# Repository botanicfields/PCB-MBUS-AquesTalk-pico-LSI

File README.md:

# PCB-MBUS-AquesTalk-pico-LSI
# M5Stack用 AquesTalk pico LSIモジュール基板
M-BUS Module of AquesTalk pico LSI for M5Stack

# 1. 概要
　市販の音声合成専用LSI「AquesTalk pico LSI」（別売）をM-BUSモジュールとしてM5Stackに取り付けるための半完成基板です。  
　AquesTalk pico LSIの詳細は、データシートを参照ください。  
[Data Sheet: 音声合成 LSI 「AquesTalk pico LSI」ATP3011](https://www.a-quest.com/archive/manual/atp3011_datasheet.pdf)  
[Data Sheet: 音声合成 LSI 「AquesTalk pico LSI」ATP3012](https://www.a-quest.com/archive/manual/atp3012_datasheet.pdf)

### 基板V04の変更点
　2022年10月末から基板V04を提供しています。詳細は、スピーカーの接続の項を参照ください。

- ハンダジャンパJP8, JP9を追加しました。
- ランドJ5を追加しました。

### 委託販売
（スイッチサイエンス扱い）[M5Stack用 AquesTalk pico LSI モジュール基板](https://www.switch-science.com/collections/marketplace/products/7624)

### 動作例
（YouTube）["AquesTalk pico LSI" speaks date and time](https://youtu.be/DpDmjqU7RUM)  
（YouTube）[M-Bus Module of AquesTalk pico LSI drives the built-in speaker of M5Stack](https://youtu.be/npRQEOJegkY)  
（YouTube）[M-Bus Module of AquesTalk pico LSI for M5Stack](https://youtu.be/YfKwWRxrInM)  
（YouTube）[M-Bus Module of AquesTalk pico LSI for M5Stack on Core2](https://youtu.be/zXvg78xzJ5E)

### 組み立て例
　組み立てにはハンダ付けが必要です。

左側: ATP3011を搭載、音声アナログ信号をGPIO35に入力するためJP5をショート  
右側: ATP3012を搭載、音声アナログ信号をGPIO35に入力するためJP6をショート  
   
写真右: M5Stack 取り付け例、J4に外部スピーカを接続  

## 1.1 特徴
- AquesTalk pico LSI（28ピンDIPタイプ）1個を搭載できます。
- ATP3011, ATP3012の両方に対応しています。
- パワーアンプ（LM4871）を内蔵し、スピーカーを直接駆動できます。
- AquestTalk pico LSIを3.3Vで動作させ、M-BUSに直結できます。
- プロトモジュールのモールド（別売）を流用し、M5Stackに取り付けできます。
- スピーカー以外のケーブル接続が不要です。
- DIP スイッチで動作モード・通信モードを設定できます。
- インタフェースをI2C, UART, SPIから選べます。
- AquesTalk pico LSIの音声出力をM-BUSから取り込めます。
- M5StackのリセットでAquesTalk pico LSIをリセットします。
- スタンドアロンモードのためのランドがあります。

DIP: Dual In-line Package  
I2C: Inte-Integrated Circuit  
UART: Universal Asynchronous Receiver Transmitter  
SPI: Serial Peripheral Interface

## 1.2 商品内容
- M-BUS モジュール基板（半完成品）1枚  
- スピーカーケーブル 1組（2ピンPH相当コネクタ付き、20cm片端ストリップ済）  
（秋月電子通商扱い）[コネクタ付コード２Ｐ（Ａ）（赤白）DG01032-0045-01(C5679)](https://akizukidenshi.com/catalog/g/gC-05679/)
- 説明書 1部

※ AquesTalk pico LSIは付属しません。  
※ プロトモジュールのモールドは付属しません。  
※ スピーカーは付属しません。

### 商品写真
写真左: 内容物(基板V4)、写真右: 基板V4裏面  

## 1.3 別途必要なもの
- AquesTalk pico LSI（秋月電子通商扱い）  
[音声合成ＬＳＩ　ＡＴＰ３０１１Ｆ１－ＰＵ（ゆっくりな女性の音声）
ATP3011F1-PU](https://akizukidenshi.com/catalog/g/gI-06220/)  
[音声合成ＬＳＩ　ＡＴＰ３０１１Ｆ４－ＰＵ（かわいい女性の音声）
ATP3011F4-PU](https://akizukidenshi.com/catalog/g/gI-05665/)  
[音声合成ＬＳＩ　ＡＴＰ３０１１Ｍ６－ＰＵ（男性の音声）
ATP3011M6-PU](https://akizukidenshi.com/catalog/g/gI-06225/)  
[音声合成ＬＳＩ　ＡＴＰ３０１２Ｆ６－ＰＵ（女性の音声明瞭版）
ATP3012F6-PU](https://akizukidenshi.com/catalog/g/gI-09973/)  
[音声合成ＬＳＩ　ＡＴＰ３０１２Ｒ５－ＰＵ（小型ロボットの音声）
ATP3012R5-PU](https://akizukidenshi.com/catalog/g/gI-11517/)
- プロトモジュール  
（スイッチサイエンス扱い）[M5Stack用プロトモジュール](https://www.switch-science.com/catalog/3650/)
- スピーカー  
4～8Ω程度、1W以上が望ましいです。
- 工具  
ハンダ、ハンダごて、ニッパー、六角レンチ(1.5mm)、カッター、ピンセットなど
- M5Stack  
サンプルプログラムは、主にM5Stack Core Basicで動作を確認しています。
- Arudino-IDEが動作する環境  

# 2. モジュール基板の組み立て

## 2.1 AquesTalk pico LSI の取り付け
　別売のAquestTalk pico LSI（28ピンDIPタイプ）1個を取り付けます。ATP3011とATP3012とでは挿入する穴が異なります。基板上のシルク印刷に従ってピンを挿入しハンダ付けします。モジュール基板裏面から飛び出しているピンを短く切ってください。

左: ATP3011, 右: ATP3012  

### ICソケットは使用できません
　ICソケットを使用すると、プロトモジュールのモールドには収まらなくなります。収まらなくなることを承知の上で1列タイプのICソケットを使用するとATP3011とATP3012を差し換えることができます。モジュール基板裏面からのピンの飛び出しの対処も大変になります。

- ICソケット（秋月電子通商扱い）  
[丸ピンＩＣ用ソケット　（シングル１４Ｐ）　１×１４　
6604S-14](https://akizukidenshi.com/catalog/g/gP-03470/)  
[丸ピンＩＣ用ソケット　（シングル１４Ｐ）　１×１４　
JS-11791SFTD-14](https://akizukidenshi.com/catalog/g/gP-11451/)  ※在庫限り  

## 2.2 モールドの取り付け
　プロトモジュールのモールドおよびネジ4本（別売）を流用して、M5StackのM-BUSモジュールに仕立てることができます。モールドを基板に取り付ける前に、ボリュームやスピーカー出力コネクタの部分をモールドから切り取ります。
### モールドの入手先（スイッチサイエンス扱い）

- [M5Stackプロトモジュール用プラスチックフレーム（2個入）](https://www.switch-science.com/collections/m5stack/products/8450)
- [M5Stack用プロトモジュール [M001]](https://www.switch-science.com/collections/m5stack/products/3650)

## 2.3 スピーカーの接続

- 付属のケーブルでJ4とスピーカー（付属せず）を接続します。GNDには接続しないでください。
- （基板V4）J5にスピーカーを接続することができます。GNDには接続しないでください。
- （基板V4）M5Stack(Core1)の内蔵スピーカーを使用できます。ATP3011の場合はJP8を、ATP3012の場合はJP9をショートしてください。M5Stack本体からGPIO25を使用しないでください。Core2は内蔵スピーカーの回路構成が異なるため、この方法は使えません。  

左側: ATP3011を搭載、GPIO25, 35に接続するためJP8, JP5をショート(基板V4)  
右側: ATP3012を搭載、GPIO35に接続するためJP6をショート、J5にスピーカを接続(基板V4)  

参考：写真のスピーカーは以下を両面テープで固定しています。ATP3012の場合かろうじて収まります。上に重ねるモジュールやボトムによっては収まりません。  
（秋月電子通商扱い）  
[マイクロスピーカー　赤／黒リード付　８Ω](https://akizukidenshi.com/catalog/g/gP-12494/)  
[マイクロスピーカー　青／白リード付　８Ω](https://akizukidenshi.com/catalog/g/gP-12495/)

### M5Stackの内蔵スピーカーについて
　M-BUSのGPIO25は、M5Stack内部のオーディオアンプを通して内蔵スピーカーに繋がっています。AquesTalk pico LSIからの音声出力をGPIO25に入力すれば、内蔵スピーカーから音声を出すことができます。ボリューム(VR)の出力を用いることで音量調節が可能です。以下の写真は、ATP3011を載せたモジュールにおいてGPIO25とボリューム出力を導線で接続した例です。ATP3012の場合は、ボリューム出力は1つ左側のピンです。基板V4のJP8, JP9はこれらの導線を埋め込んだものです。M5Stack自身がGPIO25を使わないことが前提です。Core2は内蔵スピーカーの回路構成が異なるため、この方法は使えません。

VR: Variable Resistor

## 2.4 その他の端子
- J2は、ICSPです。コネクタ等は実装していません。使用にはピンヘッダをハンダ付けするなどの処置が必要です。ICSPのVCCはAquesTalk pico LSIの電源端子に繋がっているほか、M-BUSの3.3Vにも繋がっています。ICSPは、モジュール基板をM5Stackから切り離し、単体にして接続してください。  
ICSP: In Circuit Serial Programming  

- J3は、スタンドアロンモードで使用するPC0-3およびGNDの端子です。コネクタ等は実装していません。使用には信号ケーブルを直接ハンダ付けするなどの処置が必要です。

### スタンドアロン接続例
　M5Stack用 AquesTalk pico LSIモジュールをM-Busエクステンションに載せ、ダイオードマトリクススイッチ16基板を接続しています。M5Stackの電源とリセットを使用しています。  
（スイッチサイエンス扱い）[M-Busエクステンション基板キット](https://www.switch-science.com/catalog/7371/)  
（スイッチサイエンス扱い）[ダイオードマトリクススイッチ16基板](https://www.switch-science.com/catalog/7626/)  

# 3. モジュールの設定

## 3.1 DIPスイッチによる動作モード・通信モードの設定
　動作モードおよび使用するインタフェース（通信モード）に合わせて、モジュール基板上のDIPスイッチを設定します。設定にはピンセットなどが必要です。おすすめはI2C接続です。出荷時の設定は、セーフモード・I2C接続です。DIPスイッチの設定はリセット時に反映されます。AquesTalk pico LSIのリセットはM5Stackのリセットに繋がっています。

| 1 | 2 | 3 | 4 |動作モード|通信モード|備考|
|:-:|:-:|:-:|:-:|:-:|:-:|:- |
|OFF|OFF|OFF|ON | コマンド入力モード |I2C |I2CアドレスはEEPROMに設定した値（初期値0x2E）|
|OFF|ON |OFF|ON | セーフモード |I2C |I2Cアドレスは強制的に0x2E|
|OFF|OFF|OFF|OFF| コマンド入力モード |UART|設定されたスピードで動作 (*1) |
|OFF|ON |OFF|OFF| セーフモード |UART|強制的に9600bpsで動作|
|OFF| - |ON |OFF| - | SPI mode 3 | - |
|OFF| - |ON |ON | - | SPI mode 0 |サンプルプログラムはSPI mode 0で動作|
|ON |OFF| - | - | スタンドアロンモード | - |PC0-3の信号入力によりプリセットメッセージを選択して再生|
|ON |ON | - | - | デモモード | - |プリセットメッセージを順番に自動再生|

※ 1, 2, 3, 4は、DIPスイッチの番号。DIPスイッチはON=GNDのため、ON=0, OFF=1です。  
(*1) ATP3011の場合、SLEEP解除後の'?'送信で自動設定します。ATP3012の場合EEPROMに設定します。

## 3.2 ハンダジャンパによる信号の接続
　モジュール基板裏面のジャンパJP1-JP9をハンダで短絡（クローズ）することにより、GPIOとAquesTalk pico LSIの信号ピンを接続できます。

|ジャンパ|GPIO(Core1)|GPIO(Core2)|AquesTalk pico LSI|出荷時|
|:-:|:-:|:-:|:-|:-:|
|JP1|16|13|UART-TX|オープン|
|JP2|19|38|SPI-MISO|オープン|
|JP3|5|33|SPI-SS|オープン|
|JP4|13|19|SLEEP|オープン|
|JP5|35|35|Analog Out of ATP3011|オープン|
|JP6|35|35|Analog Out of ATP3012|オープン|
|JP7|GND|GND|Shut Down of Power Amplifier|クローズ|
|JP8|25|25|Analog VR Out of ATP3011|オープン|
|JP9|25|25|Analog VR Out of ATP3012|オープン|

### JP1, JP2, JP3: インタフェース信号
　使用するインタフェースに合わせてJP1, JP2, JP3をハンダで短絡（クローズ）します。I2Cの場合はJP1, JP2, JP3を全てオープンのままで使用できます。他の用途に影響がなければJP1, JP2, JP3を短絡（クローズ）することで全てのインタフェースを使用可能です。出荷時はオープンです。

|インタフェース|JP1|JP2|JP3|AquestTalk pico LSIピン=GPIO(Core1)|AquestTalk pico LSIピン=GPIO(Core1)|
|:-:|:-:|:-:|:-:|:- |:- |
|I2C| - | - | - |SDA=21, SCL=22|SDA=21, SCL=22|
|UART|クローズ| - | - |TX=16, RX=17|TX=13, RX=14|
|SPI| - |クローズ|クローズ|SCK=18, MISO=19, MOSI=23, SS = 5|SCK=18, MISO=38, MOSI=23, SS = 33|

SDA: Serial DAta  
SCL: Serial CLock  
RX: Receive  
TX: Transmit  
MISO: Master In Slave Out  
MOSI: Master Out Slave In  
SCK: Serial ClocK  
SS: Slave Select

### JP4: SLEEP 信号
　AquesTalk pico LSIのSLEEPピンをGPIO13(Core2ではGPIO19)に接続できます。SLEEP=LowでAquesTalk pico LSIがスリープ状態になります。ATP3011のUART接続において9600bpsより速い速度が必要な場合、「セーフモード」ではなく「コマンド入力モード」に設定し、速度設定のためにSLEEPを使用します。出荷時はオープンです。

### JP5, JP6: 音声信号の取り込み
　AquesTalk pico LSIの音声出力をGPIO35経由でM5Stackに取り込むことができます。ATP3011の場合はJP5を、ATP3012の場合はJP6をハンダで短絡（クローズ）します。出荷時はオープンです。

### JP7: パワーアンプのシャットダウン
　JP7がクローズ（短絡）の場合、パワーアンプのシャットダウン（SD: Shut Down）信号をGNDに接続しパワーアンプを常に動作状態とします。JP7のハンダを取り除く（オープン）にすると、AquesTalk pico LSIのPLAY信号（負極性）がシャットダウン信号となり、パワーアンプの消費電力を減らすことができます。この設定では音声再生の前後でノイズが発生します。出荷時はクローズ（短絡）です。

### JP8, JP9（基板V4）: M5Stack(Core1)の内蔵スピーカーへの接続
　AquesTalk pico LSIの音声出力をボリューム調節後にGPIO25経由でM5Stack内蔵アンプ・スピーカーに接続することができます。ATP3011の場合はJP8を、ATP3012の場合はJP9をハンダで短絡（クローズ）します。出荷時はオープンです。

# 4. サンプルプログラム
　AquesTalk pico LSIをM5Stackに接続し、I2C(Wire), UART(Serial), SPIで動作させるプログラムです。デモの内容は同じです。Arduino-IDE環境で使用します。モジュール基板の設定を予め使用するインタフェースに合わせておく必要があります。

### BF-034_Wireフォルダ
　AqeusTalk pico LSIをI2Cで動作させるサンプルプログラムです。

### BF-034_Serialフォルダ
　AqeusTalk pico LSIをUARTで動作させるサンプルプログラムです。

### BF-034_Spiフォルダ
　AqeusTalk pico LSIをSPIで動作させるサンプルプログラムです。

### BF-034_Core2_Wireフォルダ
　Core2にモジュールを装着して、AqeusTalk pico LSIをI2Cで動作させるサンプルプログラムです。M5Stack Core1との違いは以下です

- includeするヘッダーファイル
- WireのGPIOピン番号、SleepのGPIOピン番号

## 4.1 ボタン操作 .. loop()
　ボタンを押すと、ソースコードのpreset_msgを発声します。初期値はpreset_msg[0]です。

| M5 | ボタン | 停止中 | 発声中 |
|:-:|:-:|:-:|:-:|
|M5Stack| A   | 1つ前のpreset_msgを発声 | 発声を中断して1つ前のpreset_msgを発声 |
|M5Stack| B   | 現在のpreset_msgを発声 | 発声を中断して停止 |
|M5Stack| C   | 1つ後のpreset_msgから連続して発声 | 発声を中断して1つ後のpreset_msgから連続して発生 |

## 4.2 setup()
- SLEEP ピンをHighにする（デフォルト: 実行する）  
　JP4をクローズ（短絡）すると、GPIO13(Core2ではGPIO19)とAquesTalk pico LSIのSLEEPピンとが接続します。SLEEPをHIGHにしてSLEEPでない状態にします。

- UARTスピードを設定（ATP3011が対象。UARTのみ。デフォルト: 実行しない）  
　AquesTalk pico LSI (ATP3011) のUARTスピードを設定します。GPIO13(Core2ではGPIO19)がAquesTalk pico LSIのSLEEPピンと接続している必要があります。

- UARTスピードを書き換え（ATP3012が対象。UARTのみ。デフォルト: 実行しない）  
　AquesTalk pico LSI (ATP3012) のUARTスピードを書き換えます。

- I2Cアドレスを書き換え（I2Cのみ。デフォルト: 実行しない）  
　AquesTalk pico LSIのI2Cアドレスを書き換えます。

- プリセットメッセージを書き込む（デフォルト: 実行しない）  
　AquesTalk pico LSIにプリセットメッセージとして、ソースコード内のpreset_msgデータを書き込みます。時間がかかります。

- EEPROMデータをダンプ（デフォルト: 実行しない）  
　AquesTalk pico LSIのEEPROMデータをシリアルモニタに表示します。時間がかかります。

- AquesTalk pico LSIのバージョンをシリアルモニタに表示

- チャイムJを発声

- チャイムKを発声

# 5. ライブラリ
　AquesTalk pico LSIを使用するためのライブラリです。

## 5.1 BF_AquesTalkPico.h
　I2C, UART, SPI共通の基本クラスです。接続するインタフェースに依ってI2C(Wire), UART(Serial), SPIのいずれかの派生クラスを使用する必要があります。

### (1) virtual int Send(const char* msg) = 0
　AquesTalk pico LSIに文字列msgを送信します。送信の様子をシリアルモニタに出力します。純粋仮想関数として定義し、使用するインタフェースに合わせて派生クラスで実装します。

### (2) virtual size_t Recv(char* res, size_t res_size) = 0
　AquesTalk pico LSIから文字列を受信します。受信完了は、'>'または'*'で判断します。純粋仮想関数として定義し、使用するインタフェースに合わせて派生クラスで実装します。

### (3) virtual bool Busy() = 0
　発声中などAquesTalk pico LSIが処理中の場合trueを応答します。falseの場合発声が終了したと判断できます。純粋仮想関数として定義し、使用するインタフェースに合わせて派生クラスで実装します。I2C, SPIではおのずとポーリングができますが、UARTではSend()による明示的なポーリングが必要です。

### (4) int ShowRes(int res_length_to_show = 1)
　AquesTalk pico LSIからの応答をシリアルモニタに出力します。res_length_to_showに2を渡すと、応答が1文字以下の場合にシリアルモニタへの出力を抑止できます。I2C、SPIのポーリングによる応答が正常（'>', 1文字）の場合のシリアルモニタへの出力を省略できます。

### (5) int DumpEeprom()
　AquesTalk pico LSIのEEPROM (アドレス0x000-0x3FF) の値をシリアルモニタに出力します。

### (6) int WriteEeprom(int address, int data)
　AquesTalk pico LSIのEEPROMにデータを書き込みます。

### (7) int WritePresetMsg(const char* msg[], int num_of_msg)
　AquesTalk pico LSIのEEPROMにプリセットメッセージを書き込みます。書き込みの様子をシリアルモニタに出力します。

### (8)  int WriteSpeed(int speed)
　発話速度をEEPROMに設定します。50～300を設定できます。デフォルトは100です。

### (9)  int WritePause(int pause)
　文末ポーズの長さをEEPROMに設定します。256～65535を設定できます。65535を設定すると自動になります。デフォルトは65535です。

### (10) int WriteSerialSpeed(int serial_speed)
　AquesTalk pico LSI (ATP3012) のシリアル通信速度を書き換えます。デフォルトは9600です。

### (11) int WriteI2cAddress(int i2c_address)
　AquesTalk pico LSIのI2Cアドレスを書き換えます。デフォルトは0x2Eです。

## 5.2 BF_AquesTalkPicoWire.h
　AquesTalk pico LSIとI2Cでインタフェースする派生クラスです。

### int Begin(TwoWire &wire, int i2c_address = 0x2e);
　AquesTalk pico LSIを接続するI2CとI2Cアドレスを指定します。

## 5.3 BF_AquesTalkPicoSerial.h
　AquesTalk pico LSIとUARTでインタフェースする派生クラスです。

### int Begin(Stream &stream);
　AquesTalk pico LSIを接続するUARTを指定します。

## 5.4 BF_AquesTalkPicoSpi.h
　AquesTalk pico LSIとSPIでインタフェースする派生クラスです。

### int Begin(SPIClass &spi, int ss);
　AquesTalk pico LSIを接続するSPIとSSとして使用するGPIOを指定します。

# 6. BF-034_Clockフォルダ
　M5StackのLCDに日付・時刻を表示する置時計のデモです。

- リセット後はsetupの状況を表示します。setupが完了しボタンCを押すと時計表示になります。
- ボタンBで日付を音声で読み上げます。ボタンCで時刻を音声で読み上げます。

### ご注意
　WiFi動作中に発声すると電圧低下を検出してリブートすることがあります。

### 参考情報

- Qiita: [ESP32のWiFiおよびtzapu/WiFiManagerにおいて回復処理を試行錯誤した](https://qiita.com/BotanicFields/items/8a73101a8bfe51e57f67)
- Qiita: [ESP32 において NTP の時刻同期を捕まえて RTC を更新する](https://qiita.com/BotanicFields/items/f1e28af5a63e4ccf7023)
- Qiita: [M5Atom, M5Stack Core 用の I2C リアルタイムクロック基板を作って動かす](https://qiita.com/BotanicFields/items/dc35e12423be8f6e9b4e)

# 7. 参考
- Qiita: [AquesTalk pico LSI を M5Stack の I2C, UART, SPI で動かす](https://qiita.com/BotanicFields/items/fff644f408c291e5a5f0)

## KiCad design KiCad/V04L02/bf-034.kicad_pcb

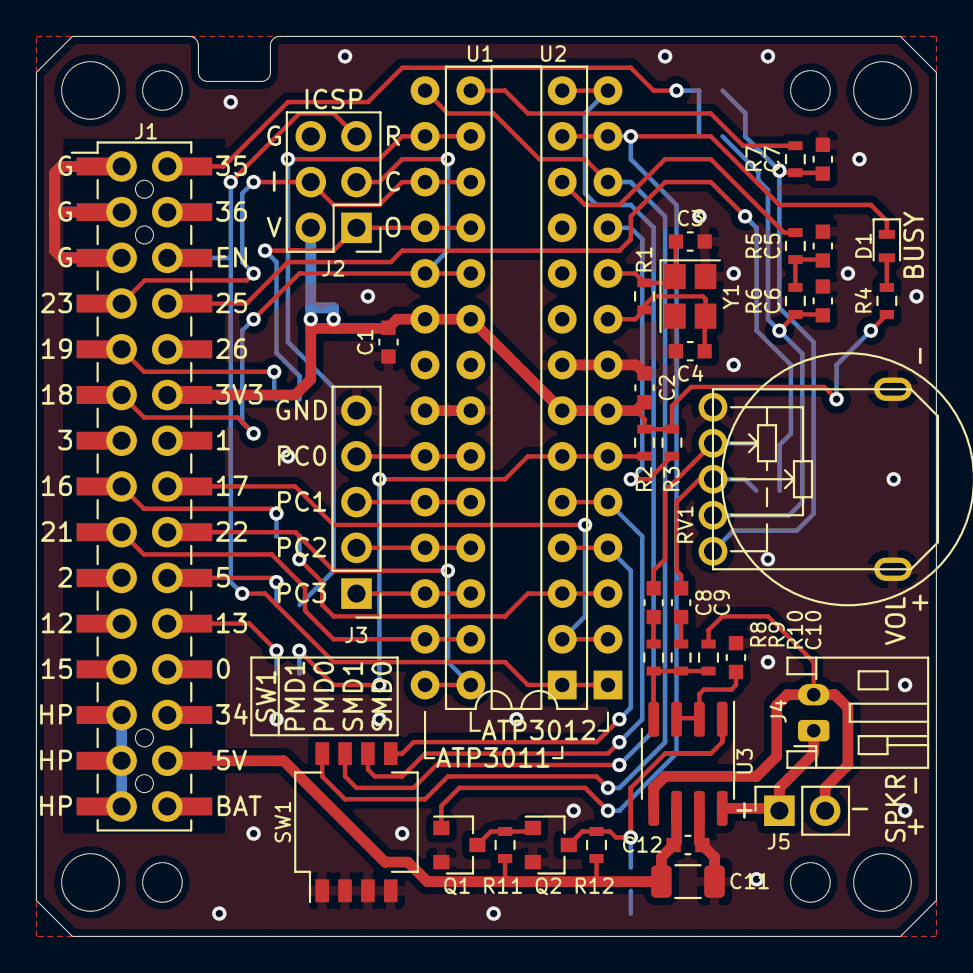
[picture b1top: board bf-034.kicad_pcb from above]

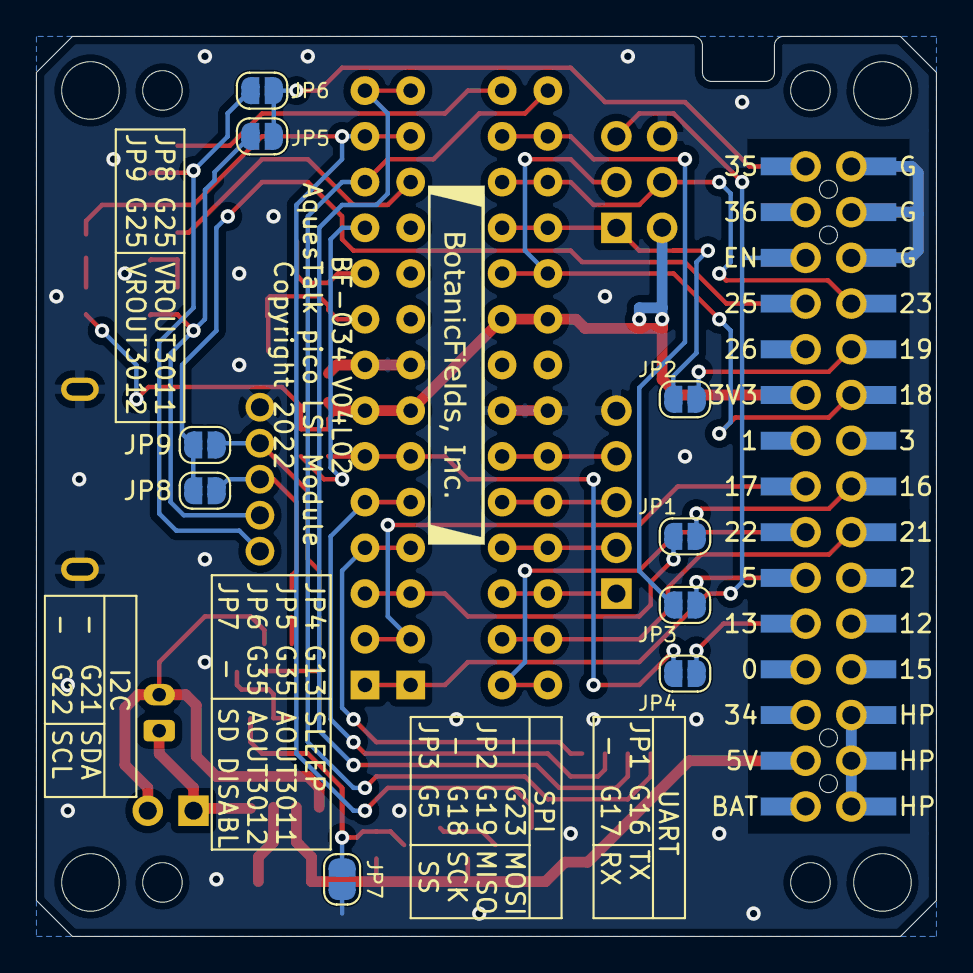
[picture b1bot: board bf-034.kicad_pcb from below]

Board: 2 copper layers, 50.0 x 50.0 mm, 55 parts (9 on the bottom side), 48 nets.

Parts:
C1, C2, C5, C12: 100n; BF@C_0603_1608Metric
C3, C4: 10p; BF@C_0603_1608Metric
C6: 22n; BF@C_0603_1608Metric
C7: 10n; BF@C_0603_1608Metric
C8, C9: 33n; BF@C_0603_1608Metric
C10: 1u; BF@C_0603_1608Metric
C11: 22u; C_1206_3216Metric
D1: BUSY; BF@LED_0603_1608Metric
H1, H2, H3, H4: MountingHole; BF@MountingHole_3.2mm_M3
H5, H6, H7, H8: MountingHole; BF@MountingHole_2.2mm_M2
J1: M-BUS; BF@M5Stack_MBUS
J2: ICSP; PinHeader_2x03_P2.54mm_Vertical
J3: PRESET; PinHeader_1x05_P2.54mm_Vertical
J4: SPKR; JST_PH_S2B-PH-K_1x02_P2.00mm_Horizontal
J5: SPKR; PinSocket_1x02_P2.54mm_Vertical
JP1: TXD; SolderJumper-2_P1.3mm_Open_RoundedPad1.0x1.5mm
JP2: MISO; SolderJumper-2_P1.3mm_Open_RoundedPad1.0x1.5mm
JP3: SS; SolderJumper-2_P1.3mm_Open_RoundedPad1.0x1.5mm
JP4: SLEEP; SolderJumper-2_P1.3mm_Open_RoundedPad1.0x1.5mm
JP5: AOUT3011; SolderJumper-2_P1.3mm_Open_RoundedPad1.0x1.5mm
JP6: AOUT3012; SolderJumper-2_P1.3mm_Open_RoundedPad1.0x1.5mm
JP7: SD_DISABLE; SolderJumper-2_P1.3mm_Open_RoundedPad1.0x1.5mm
JP8: VROUT3011; SolderJumper-2_P1.3mm_Open_RoundedPad1.0x1.5mm
JP9: VROUT3012; SolderJumper-2_P1.3mm_Open_RoundedPad1.0x1.5mm
Q1, Q2: DTC143Z; SOT-23
R1: 1M; BF@R_0603_1608Metric
R2, R3, R11, R12: 10k; BF@R_0603_1608Metric
R4, R6: 2.2k; BF@R_0603_1608Metric
R5: 470; BF@R_0603_1608Metric
R7: 3.3k; BF@R_0603_1608Metric
R8, R9: 22k; BF@R_0603_1608Metric
R10: 68k; BF@R_0603_1608Metric
RV1: 10kA; BF@RK10J
SW1: MODE; SW_DIP_SPSTx04_Slide_KingTek_DSHP04TS_W7.62mm_P1.27mm
U1: ATP3011; DIP-28_W7.62mm
U2: ATP3012; DIP-28_W7.62mm
U3: LM4871; SOIC-8_3.9x4.9mm_P1.27mm
Y1: 16MHz; Crystal_SMD_3225-4Pin_3.2x2.5mm

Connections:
+3V3: C1.1, C2.1, J1.11, J2.2, R2.2, R3.2, R4.1, U1.7, U1.20, U2.7, U2.20
+5V: C11.1, C12.1, J1.27, R11.1, R12.1, U3.6
/AOUT_3011: R5.2, U1.12
/AOUT_3011_F: C6.2, JP5.1, R6.1, RV1.4
/AOUT_3011_V: C9.2, JP8.1, RV1.3
/AOUT_3012: R7.2, U2.15
/AOUT_3012_F: C7.2, JP6.1, R7.1, RV1.5
/AOUT_3012_V: C8.2, JP9.1, RV1.2
/CLK16: R3.1, U2.11
/EN: J1.5, J2.5, U1.1, U2.1
/GPIO5: J1.19, JP3.2
/GPIO13: J1.21, JP4.2
/GPIO16: J1.16, JP1.2
/GPIO17: J1.15, U1.2, U2.2
/GPIO18: J1.12, J2.3, U1.19, U2.19
/GPIO19: J1.10, JP2.2
/GPIO21: J1.18, U1.27, U2.27
/GPIO22: J1.17, U1.28, U2.28
/GPIO23: J1.8, J2.4, U1.17, U2.17
/GPIO25: J1.7, JP8.2, JP9.2
/GPIO35: J1.1, JP5.2, JP6.2
/MISO: J2.1, JP2.1, U1.18, U2.18
/PC0: J3.4, U1.23, U2.23
/PC1: J3.3, U1.24, U2.24
/PC2: J3.2, U1.25, U2.25
/PC3: J3.1, U1.26, U2.26
/PMOD0: SW1.7, U1.14, U2.14
/PMOD1: SW1.8, U1.15, U2.12
/SD: JP7.1, Q2.3, R12.2, U3.1
/SMOD0: SW1.5, U1.4, U2.4
/SMOD1: SW1.6, U1.5, U2.5
/TXD: JP1.1, U1.3, U2.3
/~PLAY: D1.1, Q1.1, U1.13, U2.13
/~SLEEP: JP4.1, R2.1, U1.6, U2.6
/~SS: JP3.1, U1.16, U2.16
GND: C1.2, C2.2, C3.2, C4.2, C5.1, C6.1, C7.1, C10.1, C11.2, C12.2, J1.2, J1.4, J1.6, J2.6, J3.5, JP7.2, Q1.2, Q2.2, RV1.1, RV1.6, SW1.1, SW1.2, SW1.3, SW1.4, U1.8, U1.22, U2.8, U2.22, U3.7, Y1.2, Y1.4
unnamed: C3.1, R1.2, U2.10, Y1.1
unnamed: C4.1, R1.1, U2.9, Y1.3
unnamed: C5.2, R5.1, R6.2
unnamed: C8.1, R8.2
unnamed: C9.1, R9.2
unnamed: C10.2, U3.2, U3.3
unnamed: D1.2, R4.2
unnamed: J4.1, J5.1, U3.8
unnamed: J4.2, J5.2, R10.1, U3.5
unnamed: Q1.3, Q2.1, R11.2
unnamed: R8.1, R9.1, R10.2, U3.4
VBUS: J1.26, J1.28, J1.30

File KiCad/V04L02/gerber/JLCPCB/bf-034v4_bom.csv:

Comment,Designator,Footprint,LCSC
1u,C10,bf:BF@C_0603_1608Metric,C15849
22u,C11,Capacitor_SMD:C_1206_3216Metric,C5672
100n,"C1,C2,C5,C12",bf:BF@C_0603_1608Metric,C14663
10p,"C3,C4",bf:BF@C_0603_1608Metric,C1634
22n,C6,bf:BF@C_0603_1608Metric,C21122
10n,C7,bf:BF@C_0603_1608Metric,C57112
33n,"C8,C9",bf:BF@C_0603_1608Metric,C21117
BUSY,D1,bf:BF@LED_0603_1608Metric,C72038
MountingHole,"H1,H2,H3,H4",bf:BF@MountingHole_3.2mm_M3,
MountingHole,"H5,H6,H7,H8",bf:BF@MountingHole_2.2mm_M2,
M-BUS,J1,bf:BF@M5Stack_MBUS,
ICSP,J2,Connector_PinHeader_2.54mm:PinHeader_2x03_P2.54mm_Vertical,
PRESET,J3,Connector_PinHeader_2.54mm:PinHeader_1x05_P2.54mm_Vertical,
SPKR,J4,Connector_JST:JST_PH_S2B-PH-K_1x02_P2.00mm_Horizontal,
SPKR,J5,Connector_PinSocket_2.54mm:PinSocket_1x02_P2.54mm_Vertical,
TXD,JP1,Jumper:SolderJumper-2_P1.3mm_Open_RoundedPad1.0x1.5mm,
MISO,JP2,Jumper:SolderJumper-2_P1.3mm_Open_RoundedPad1.0x1.5mm,
SS,JP3,Jumper:SolderJumper-2_P1.3mm_Open_RoundedPad1.0x1.5mm,
SLEEP,JP4,Jumper:SolderJumper-2_P1.3mm_Open_RoundedPad1.0x1.5mm,
AOUT3011,JP5,Jumper:SolderJumper-2_P1.3mm_Open_RoundedPad1.0x1.5mm,
AOUT3012,JP6,Jumper:SolderJumper-2_P1.3mm_Open_RoundedPad1.0x1.5mm,
SD_DISABLE,JP7,Jumper:SolderJumper-2_P1.3mm_Open_RoundedPad1.0x1.5mm,
VROUT3011,JP8,Jumper:SolderJumper-2_P1.3mm_Open_RoundedPad1.0x1.5mm,
VROUT3012,JP9,Jumper:SolderJumper-2_P1.3mm_Open_RoundedPad1.0x1.5mm,
DTC143Z,"Q1,Q2",Package_TO_SOT_SMD:SOT-23,C15236
1M,R1,bf:BF@R_0603_1608Metric,C22935
68k,R10,bf:BF@R_0603_1608Metric,C23231
10k,"R2,R3,R11,R12",bf:BF@R_0603_1608Metric,C25804
2.2k,"R4,R6",bf:BF@R_0603_1608Metric,C4190
470,R5,bf:BF@R_0603_1608Metric,C23179
3.3k,R7,bf:BF@R_0603_1608Metric,C22978
22k,"R8,R9",bf:BF@R_0603_1608Metric,C31850
10kA,RV1,bf:BF@RK10J,
MODE,SW1,Button_Switch_SMD:SW_DIP_SPSTx04_Slide_KingTek_DSHP04TS_W7.62mm_P1.27mm,C319050
ATP3011,U1,Package_DIP:DIP-28_W7.62mm,
ATP3012,U2,Package_DIP:DIP-28_W7.62mm,
LM4871,U3,Package_SO:SOIC-8_3.9x4.9mm_P1.27mm,C7554
16MHz,Y1,Crystal:Crystal_SMD_3225-4Pin_3.2x2.5mm,C13738

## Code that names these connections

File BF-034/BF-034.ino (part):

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const int aqtp_serial_speed_safe = 9600;  // safe mode
const int aqtp_serial_speed = 76800;      // max of ATP3011, also works on ATP3012
//const int aqtp_serial_speed = 115200;   // max of ATP3012, but does not work
const int aqtp_sleep_pin = 5;  // GPIO5 for sleep control
#endif

#ifdef AQUESTALKPICOWIRE
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
#ifdef AQUESTALKPICOSERIAL
// defined by Arduino-ESP32
//  const int serial2_rx(16);  // GPIO16 as default
//  const int serial2_tx(17);  // GPIO17 as default
//  Serial2.begin(9600, SERIAL_8N1, serial2_rx, serial2_tx);
//  Serial2.begin(9600);
  if (aqtp_safe_mode)
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
#ifdef AQUESTALKPICOWIRE
// defined by M5Stack
//  const int wire_sda(21);  // GPIO21 as default
//  const int wire_scl(22);  // GPIO22 as default
//  const int wire_frequency(100000);  // 100kHz as default
//  Wire.begin(wire_sda, wire_scl, wire_frequency);
//  aqtp.Begin(Wire);  // for default
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
#ifdef AQUESTALKPICOSPI
// defined by Arduino-ESP32
//  const int vspi_sclk(18);  // SCLK = GPIO18 as default
//  const int vspi_miso(19);  // MISO = GPIO19 as default
//  const int vspi_mosi(23);  // MOSI = GPIO23 as default
//  const int vspi_ss(5);     // SS   = GPIO5  as default
//  vspi->begin(vspi_sclk, vspi_miso, vspi_mosi, vspi_ss);
  vspi.begin();
  aqtp.Begin(vspi, vspi_ss);
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
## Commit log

2021-08-29 first upload
    BF-034 code
2021-09-19 v2.0
    EEPROM, SLEEP
2021-11-06 test
2021-11-14 Read me
    revised
2021-11-14 image
    add image
2021-11-14 Update README.md
    Read Me
2021-11-14 PCB
    add PCB data
2021-11-21 ADC wave
    add ADC wave demo
2021-11-22 image
    update image
2021-11-22 DOC updated
2021-11-23 example
    refine
2021-11-23 examples
    refine
2021-11-26 DOC
    updated
2021-11-30 example
    add example clock
2021-11-30 example
    update example clock
2021-12-01 Update BF_M5StackTableClock.cpp
    comment out GPIO35
2021-12-04 example
    add Core2_Wire
2021-12-05 exmaple
    update Core2_Wire
2021-12-18 examples
    add unsigned related to millis()
2022-08-28 examples updated
    add busy()
2022-08-28 adcwave
    delete old files
2022-08-28 Update README.md
    delete description for M5Atom
2022-08-29 README.md
    how to use built-in speaker of M5Stack
2022-09-08 Update BF-034_Clock.ino
    Misjudgment of wm.autoconnect() results
2022-09-25 BF_AquesTalkPico.cpp
    add WriteSpeed(), WeitePause()
2022-09-25 typos
    update REAME.md, etc,
2022-10-16 PCB V04
    add PCB V04
2022-11-01 Update README.md
    frame of proto module
2023-05-01 BF-034_Clock.ino
    Removed: Wi-Fi check at waiting button-C
2023-11-21 README.md and Document
    add Core2 GPIO information

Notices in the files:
BF-034/BF-034.ino:
Copyright 2021 BotanicFields, Inc.
KiCad/V04L02/bf-034.kicad_pcb:
Copyright 2022 BotanicFields, Inc.
